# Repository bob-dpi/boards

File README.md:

# Boards
Some peripherals use common, off-the-shelf hardware such as
Pmod cards.  Some peripherals use custom hardware.  This
repository contains design files for peripherals that use 
custom hardware.

The [***contrib***](contrib/README.md)  directory has design
files for boards that have been contributed.  Each design is 
in its own directory, has its own LICENSE.txt, and should 
have a markdown file to describe the board.  

The [***dpi***](dpi/README.md) directory has the design files
for Demand Peripherals boards that can tolerate ringing
on long cable runs.  

<br>

| Contributed Designs from Several Sources | |
| :-- | :-- |
| <a href=contrib/pmgpiontw/pmgpio.md> Pmod compatible GPIO boards <br>  </a> | <a href=contrib/dpaamp/aamp.md> Stereo 2 Watt Amplifier with volume control <br>  </a> 
| <a href=contrib/dpd7hb/d7hb.md> Dual 7-amp H-bridge <br>  </a> | <a href=contrib/dpdrv4/drv4.md> Quad open-drain driver <br>  </a>
| <a href=contrib/dpirp8/irp8.md> Octal reflective sensor <br>  </a> | <a href=contrib/dprf315/rf315.md> Keyfob-type receiver <br>  </a>
| <a href=contrib/dprly410/rly410.md> Quad 10-amp relay card <br>  </a> | <a href=contrib/dproten/roten.md> Demand Peripherals rotary encoder with LED <br>  </a>
| <a href=contrib/dpsw4/sw4.md> Quad slide switch <br>  </a> | <a href=contrib/dptouch4/touch4.md> Quad low cost touch sensor <br>  </a>
| <a href=contrib/atxpd/atxpd.md> ATX power distribution card <br>  </a> | <a href=contrib/ddpd/ddpd.md> Molex disk-drive power distribution card <br>  </a>
| <a href=contrib/smr/smr.md> 5 volt switch mode regulator <br>  </a> | <a href=contrib/pd15/pd15.md> 15 amp power distribution card <br>  </a>
| <a href=contrib/pd25/pd25.md> 25 amp power distribution card <br>  </a> |  <a href=contrib/dpirio/irio.md> Consumer IR receiver and transmitter <br>  </a> |

<br>

| Daughter Cards from Demand Peripherals | |
| :-- | :-- |
|<a href=dpi/dpadc12/adc12.md> Octal 12-bit analog to digital converter<br>  </a> | <a href=dpi/dpdac8/dac8.md> Octal 8-bit digital to analog converter <br>  <br> </a> |
|<a href=dpi/dpei2c/ei2c.md> Ringing tolerant I2C interface<br>  </a> | <a href=dpi/dpespi/espi.md> Ringing tolerant SPI interface<br>  </a> |
|<a href=dpi/dpin32/in32.md> 32 channel binary input<br>  </a> | <a href=dpi/dpio8/io8.md> Octal input and output<br>  </a> |
|<a href=dpi/dplcd6/lcd6.md>  Six digit 7-segment display <br>  </a> | <a href=dpi/dpmega/mega.md> AVR card<br>  </a> |
|<a href=dpi/dpout32/out32.md> 32 channel binary output<br>  </a> | <a href=dpi/dpqpot/qpot.md> Quad 10K digital pot <br>  </a> |
|<a href=dpi/dprtc/rtc.md> Real-time clock with alarm <br>  </a> | <a href=dpi/dpslider4/slider4.md> Quad slide pot <br>  </a> |
|<a href=dpi/dptif/tif.md> Text interface card <br>  </a> | <a href=dpi/dpus8/us8.md> Octal HC-04 distance sensor interface <br>  </a> |

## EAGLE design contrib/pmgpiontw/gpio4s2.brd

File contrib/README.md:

# contrib
This directory has the hardware design files for peripherals that
need custom hardware.  There are also design files for some simple
accessories and for one FPGA card.  Each design is in its own directory,
has its own LICENSE.txt, and should have a markdown file that describes
the board.  

While many design use Eagle, the preferred format is KiCad.
<br>

## Peripheral Cards
[pmgpiontw](pmgpiontw/pmgpio.md): Pmod compatible GPIO boards from Demand Peripherals <br>
[dpaamp](dpaamp/aamp.md): Stereo 2 Watt Amplifier with volume control <br>
[dpd7hb](dpd7hb/d7hb.md): Dual 7-amp H-bridge <br>
[dpdrv4](dpdrv4/drv4.md): Quad open-drain driver <br>
[dpgpio4](dpgpio4/gpio4.md): Demand Peripherals quad GPIO cards <br>
[dpirio](dpirio/irio.md): Consumer IR receiver and transmitter <br>
[dpirp8](dpirp8/irp8.md): Octal reflective sensor <br>
[dprf315](dprf315/rf315.md): Keyfob-type receiver <br>
[dprly410](dprly410/rly410.md): Quad 10-amp relay card <br>
[dproten](dproten/roten.md): Demand Peripherals rotary encoder with LED <br>
[dpsw4](dpsw4/sw4.md): Quad slide switch <br>
[dptouch4](dptouch4/touch4.md): Quad low cost touch sensor <br>
<br>

## Accessories
[atxpd](atxpd/atxpd.md): ATX power distribution card <br>
[ddpd](ddpd/ddpd.md): Molex disk-drive power distribution card <br>
[smr](smr/smr.md): 5 volt switch mode regulator <br>
[pd15](pd15/pd15.md): 15 amp power distribution card <br>
[pd25](pd25/pd25.md): 25 amp power distribution card <br>
[protocards](protocards/protocards.md): Prototyping cards <br>

## FPGA Boards
[Baseboard4](Baseboard4/baseboard4.md): Demand Peripherals Spartan-3E FPGA card <br>

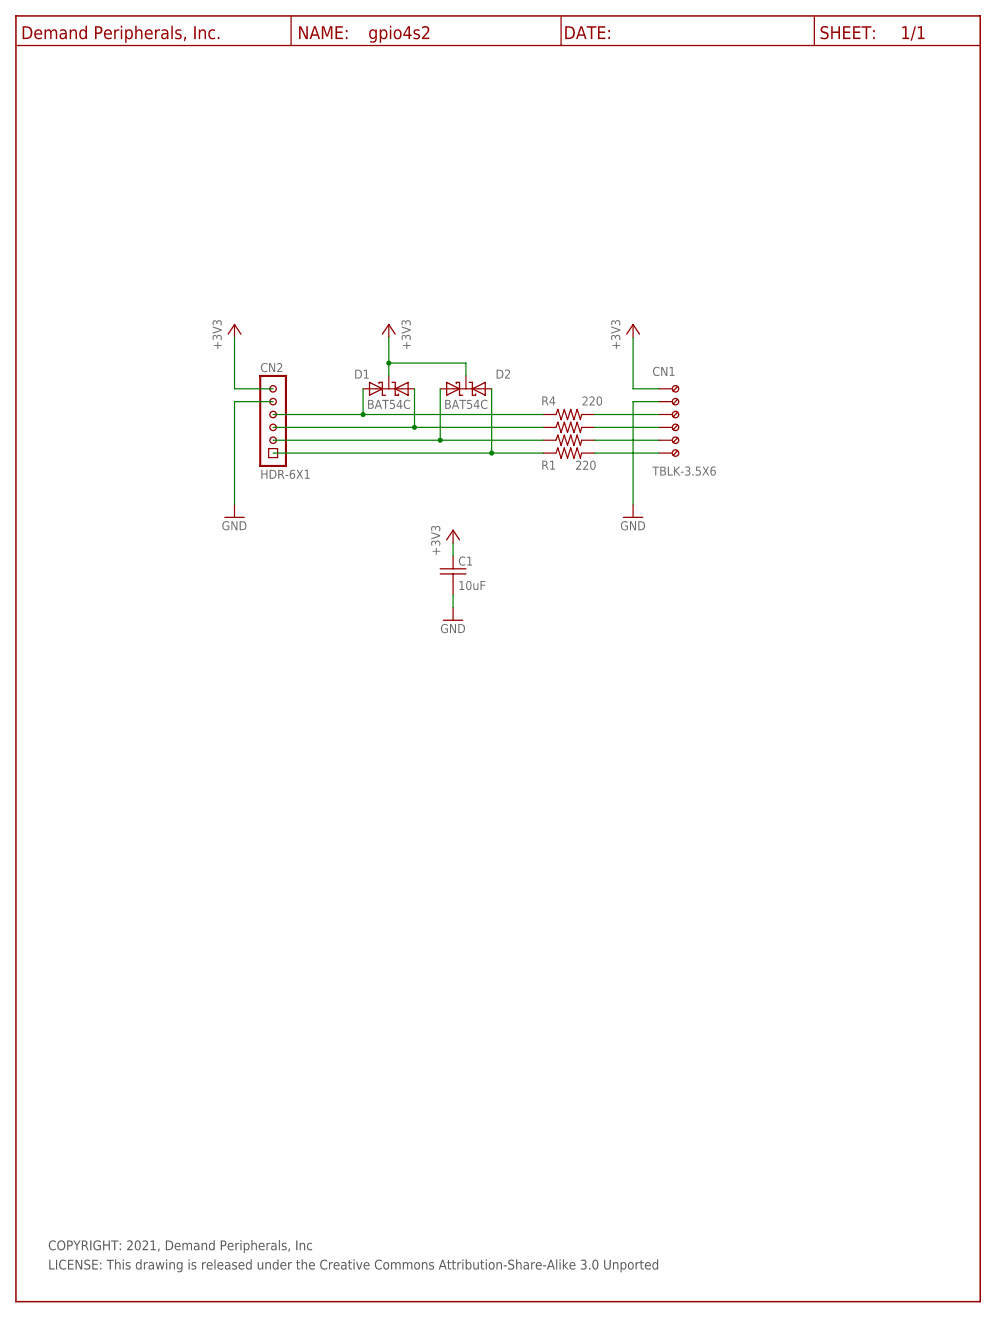
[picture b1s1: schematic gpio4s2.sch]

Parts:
C1: 10uF; C1206
CN1: TBLK-3.5X6
CN2: HDR-6X1
D1, D2: BAT54C; SOT23
R1, R2, R3, R4: 220; R0603
U$1: DP_FRAME_P; P_FRAME

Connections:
+3V3: C1.1, CN1.1 (KL), CN2.6, D1.3 (CC), D2.3 (CC)
GND: C1.2, CN1.2 (KL1), CN2.5
unnamed: CN1.3 (KL2), R4.2
unnamed: CN1.4 (KL3), R3.2
unnamed: CN1.5 (KL4), R2.2
unnamed: CN1.6 (KL5), R1.2
unnamed: CN2.4, D1.1 (A1), R4.1
unnamed: CN2.3, D1.2 (A), R3.1
unnamed: CN2.2, D2.1 (A1), R2.1
unnamed: CN2.1, D2.2 (A), R1.1

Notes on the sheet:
COPYRIGHT: 2021, Demand Peripherals, Inc
LICENSE: This drawing is released under the Creative Commons Attribution-Share-Alike 3.0 Unported

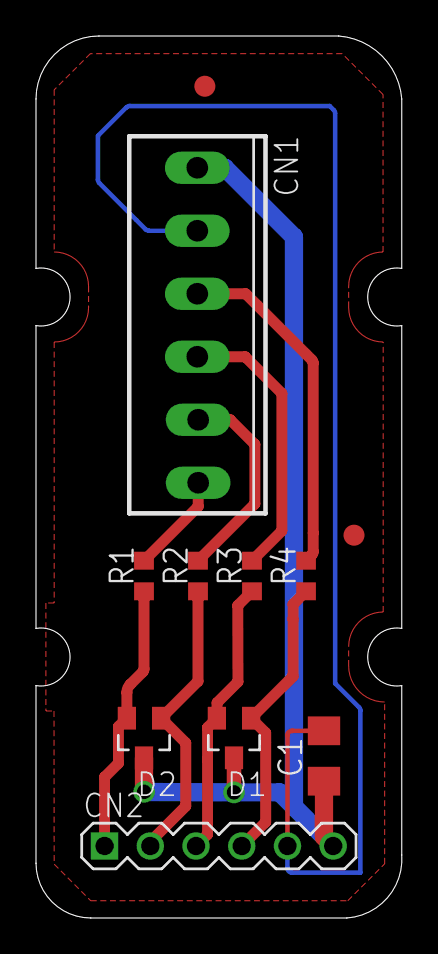
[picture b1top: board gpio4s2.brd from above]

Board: 2 copper layers, 20.3 x 49.0 mm, 13 parts (1 on the bottom side), 10 nets.

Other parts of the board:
U$2: DPI-2
U$3, U$8: FIDUCIAL

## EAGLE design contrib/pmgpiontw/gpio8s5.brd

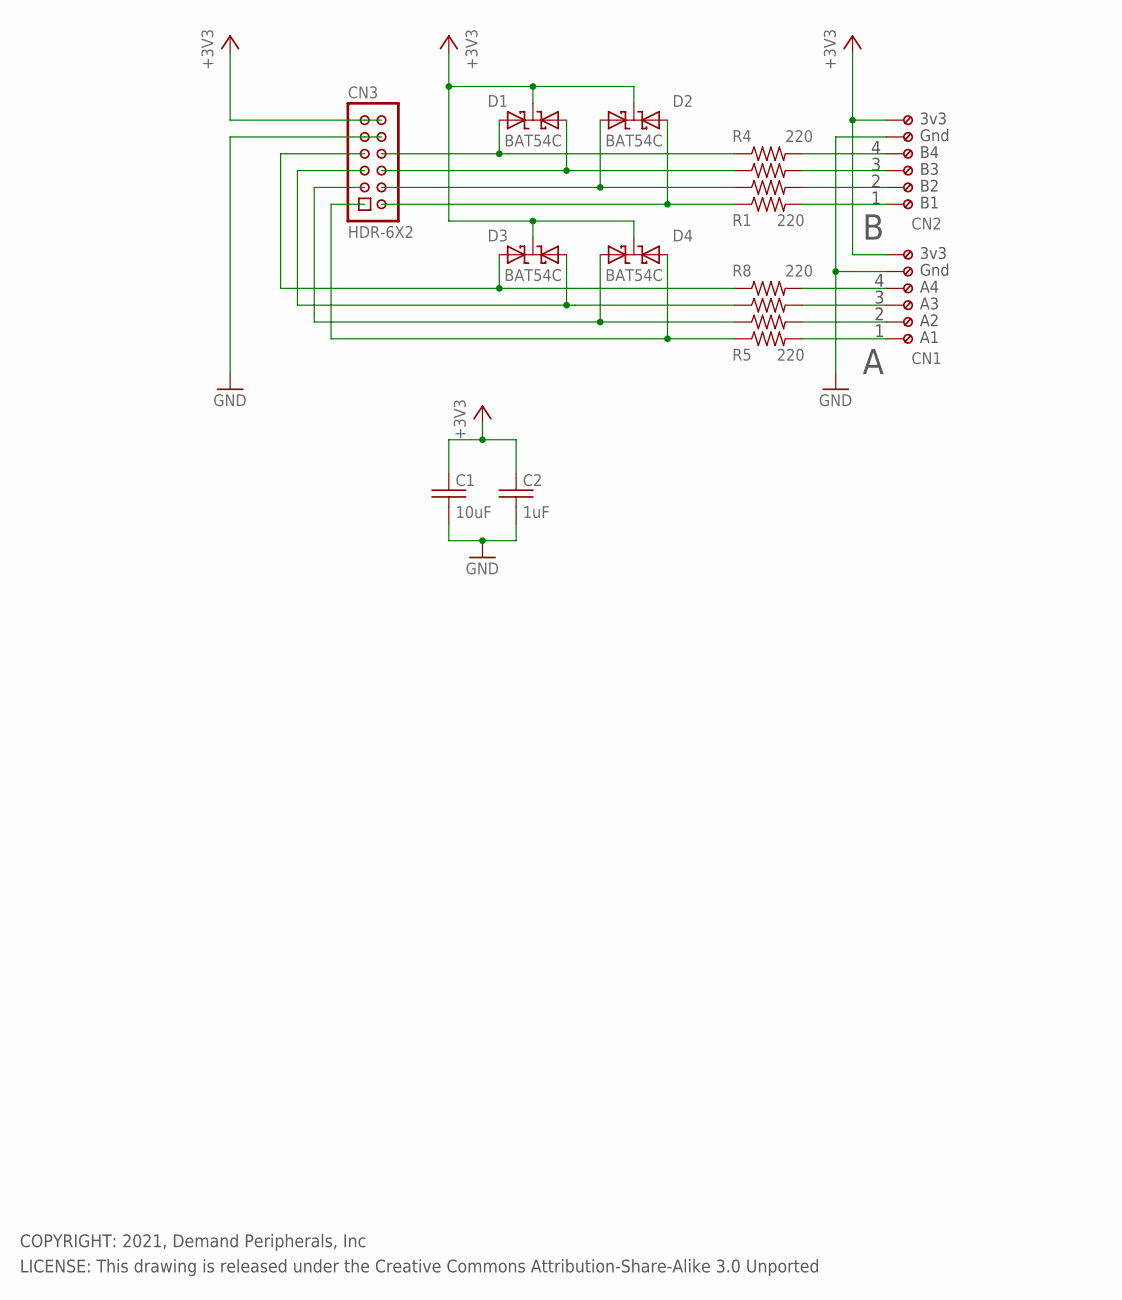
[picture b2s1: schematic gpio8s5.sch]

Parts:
C1: 10uF; C1206
C2: 1uF; C0603
CN1, CN2: TBLK-3.5X6
CN3: HDR-6X2
D1, D2, D3, D4: BAT54C; SOT23
R1, R2, R3, R4, R5, R6, R7, R8: 220; R0603

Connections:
+3V3: C1.1, C2.1, CN1.1 (KL), CN2.1 (KL), CN3.11, CN3.12, D1.3 (CC), D2.3 (CC), D3.3 (CC), D4.3 (CC)
GND: C1.2, C2.2, CN1.2 (KL1), CN2.2 (KL1), CN3.9, CN3.10
unnamed: CN2.3 (KL2), R4.2
unnamed: CN2.4 (KL3), R3.2
unnamed: CN2.5 (KL4), R2.2
unnamed: CN2.6 (KL5), R1.2
unnamed: CN3.7, D3.1 (A1), R8.1
unnamed: CN3.5, D3.2 (A), R7.1
unnamed: CN3.3, D4.1 (A1), R6.1
unnamed: CN3.1, D4.2 (A), R5.1
unnamed: CN1.3 (KL2), R8.2
unnamed: CN1.4 (KL3), R7.2
unnamed: CN3.8, D1.1 (A1), R4.1
unnamed: CN3.6, D1.2 (A), R3.1
unnamed: CN1.5 (KL4), R6.2
unnamed: CN3.4, D2.1 (A1), R2.1
unnamed: CN3.2, D2.2 (A), R1.1
unnamed: CN1.6 (KL5), R5.2

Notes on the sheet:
COPYRIGHT: 2021, Demand Peripherals, Inc
LICENSE: This drawing is released under the Creative Commons Attribution-Share-Alike 3.0 Unported
Gnd
3v3

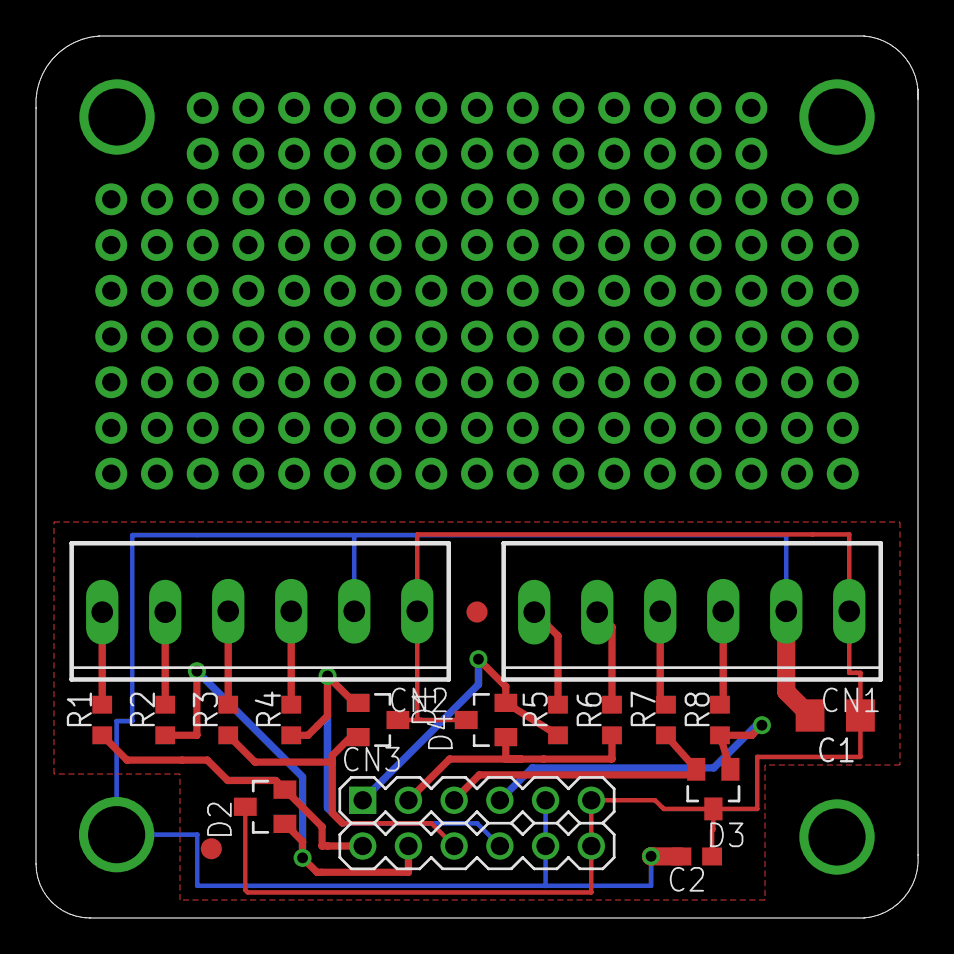
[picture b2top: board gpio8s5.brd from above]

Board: 2 copper layers, 49.0 x 49.0 mm, 20 parts (0 on the bottom side), 18 nets.

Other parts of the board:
U$2: DP_FRAME_P; P_FRAME
U$3, U$8: FIDUCIAL

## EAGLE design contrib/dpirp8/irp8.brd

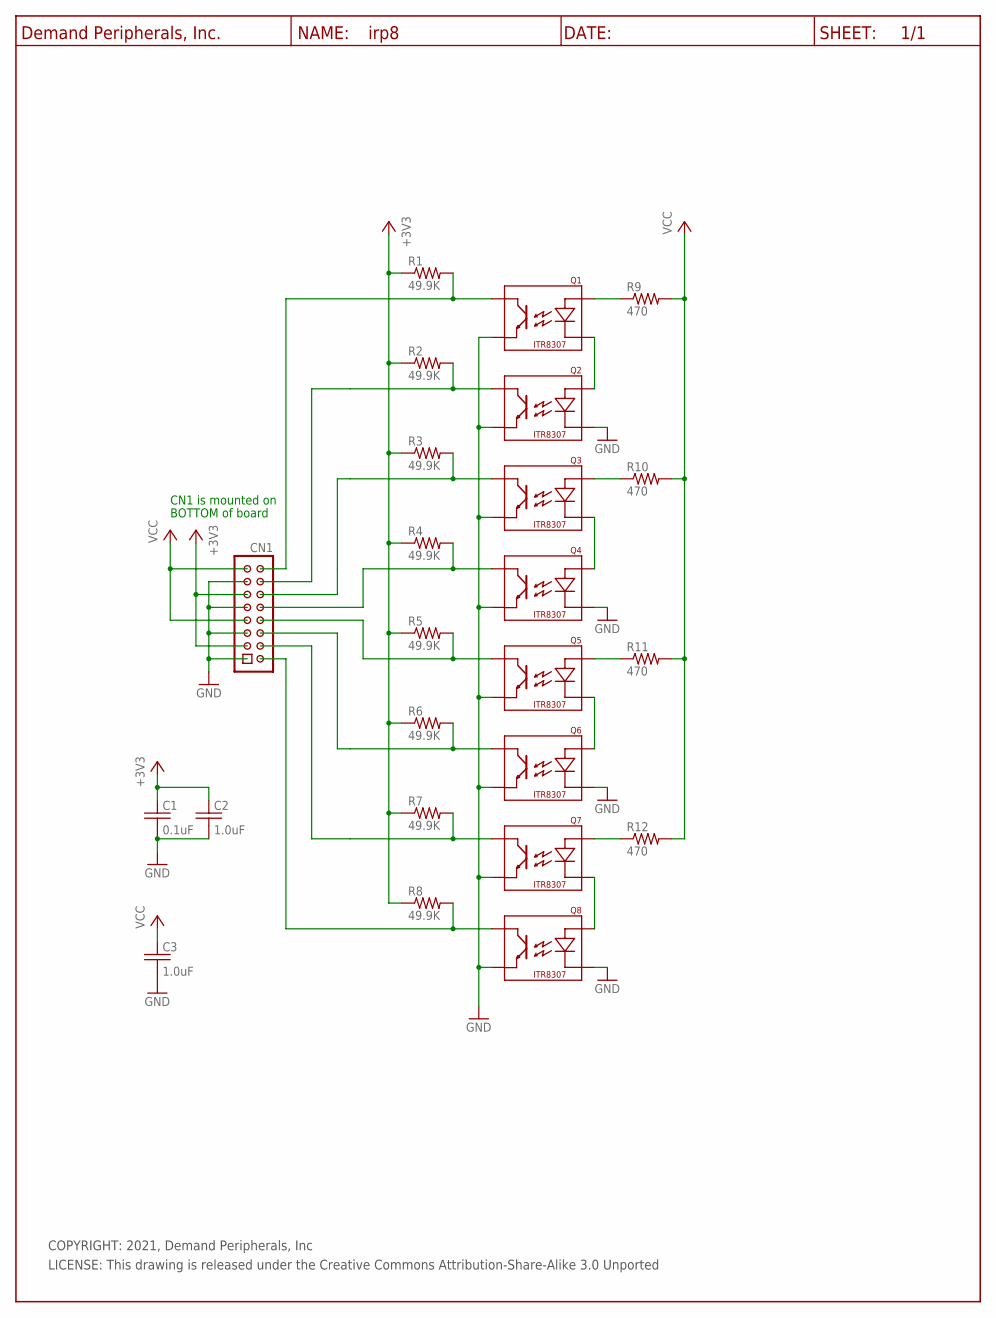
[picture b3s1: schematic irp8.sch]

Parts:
C1: 0.1uF; C0603
C2, C3: 1.0uF; C0603
CN1: HDR-8X2-SHR; HDR-8X2
Q1, Q2, Q3, Q4, Q5, Q6, Q7, Q8: ITR8307
R1, R2, R3, R4, R5, R6, R7, R8: 49.9K; R0603
R9, R10, R11, R12: 470; R0603
U$1: DP_FRAME_P; P_FRAME

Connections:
+3V3: C1.1, C2.1, CN1.3, CN1.11, R1.1, R2.1, R3.1, R4.1, R5.1, R6.1, R7.1, R8.1
GND: C1.2, C2.2, C3.2, CN1.1, CN1.5, CN1.9, CN1.13, Q1.P$1 (K), Q1.P$3 (CO), Q2.P$3 (CO), Q3.P$1 (K), Q3.P$3 (CO), Q4.P$3 (CO), Q5.P$1 (K), Q5.P$3 (CO), Q6.P$3 (CO), Q7.P$1 (K), Q7.P$3 (CO), Q8.P$3 (CO)
unnamed: CN1.16, Q8.P$4 (EM), R8.2
unnamed: Q2.P$2 (A), R12.1
unnamed: CN1.12, Q6.P$4 (EM), R6.2
unnamed: CN1.10, Q5.P$4 (EM), R5.2
unnamed: CN1.8, Q4.P$4 (EM), R4.2
unnamed: CN1.6, Q3.P$4 (EM), R3.2
unnamed: CN1.4, Q2.P$4 (EM), R2.2
unnamed: CN1.2, Q1.P$4 (EM), R1.2
unnamed: Q1.P$2 (A), Q2.P$1 (K)
unnamed: CN1.14, Q7.P$4 (EM), R7.2
unnamed: Q3.P$2 (A), Q4.P$1 (K)
unnamed: Q8.P$2 (A), R9.1
unnamed: Q7.P$2 (A), Q8.P$1 (K)
unnamed: Q6.P$2 (A), R10.1
unnamed: Q4.P$2 (A), R11.1
unnamed: Q5.P$2 (A), Q6.P$1 (K)
VCC: C3.1, CN1.7, CN1.15, R9.2, R10.2, R11.2, R12.2

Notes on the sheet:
COPYRIGHT: 2021, Demand Peripherals, Inc
LICENSE: This drawing is released under the Creative Commons Attribution-Share-Alike 3.0 Unported
CN1 is mounted on
BOTTOM of board

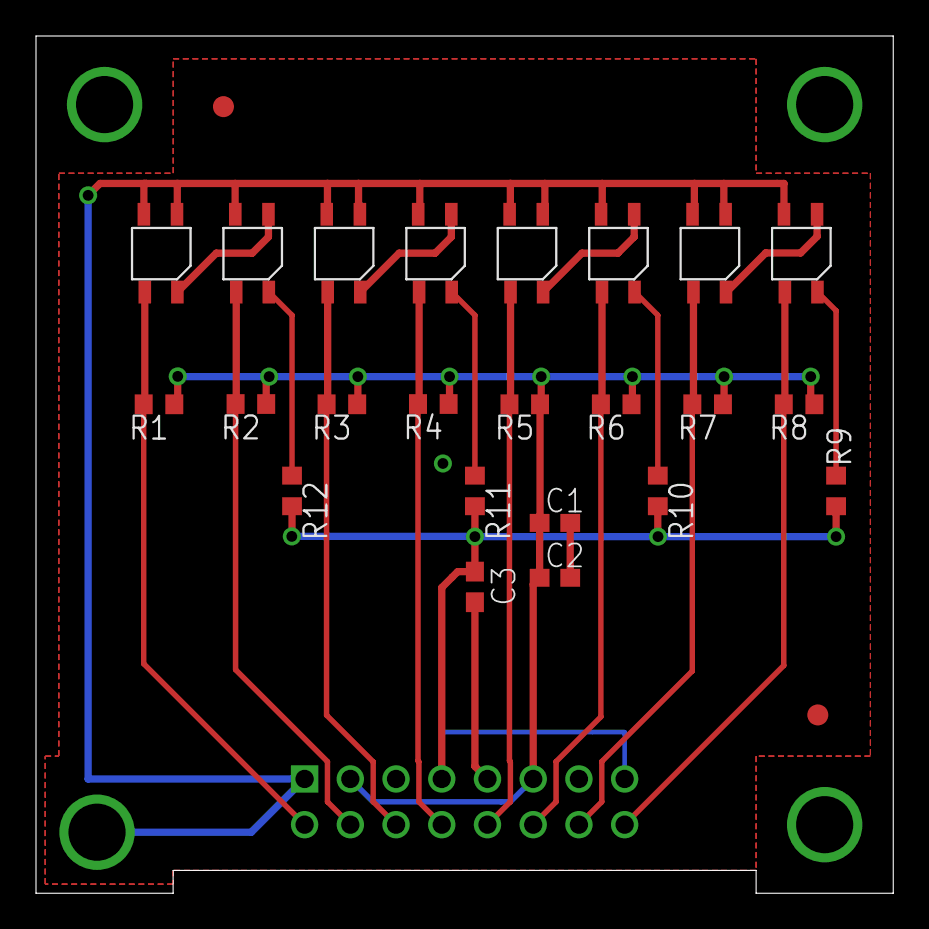
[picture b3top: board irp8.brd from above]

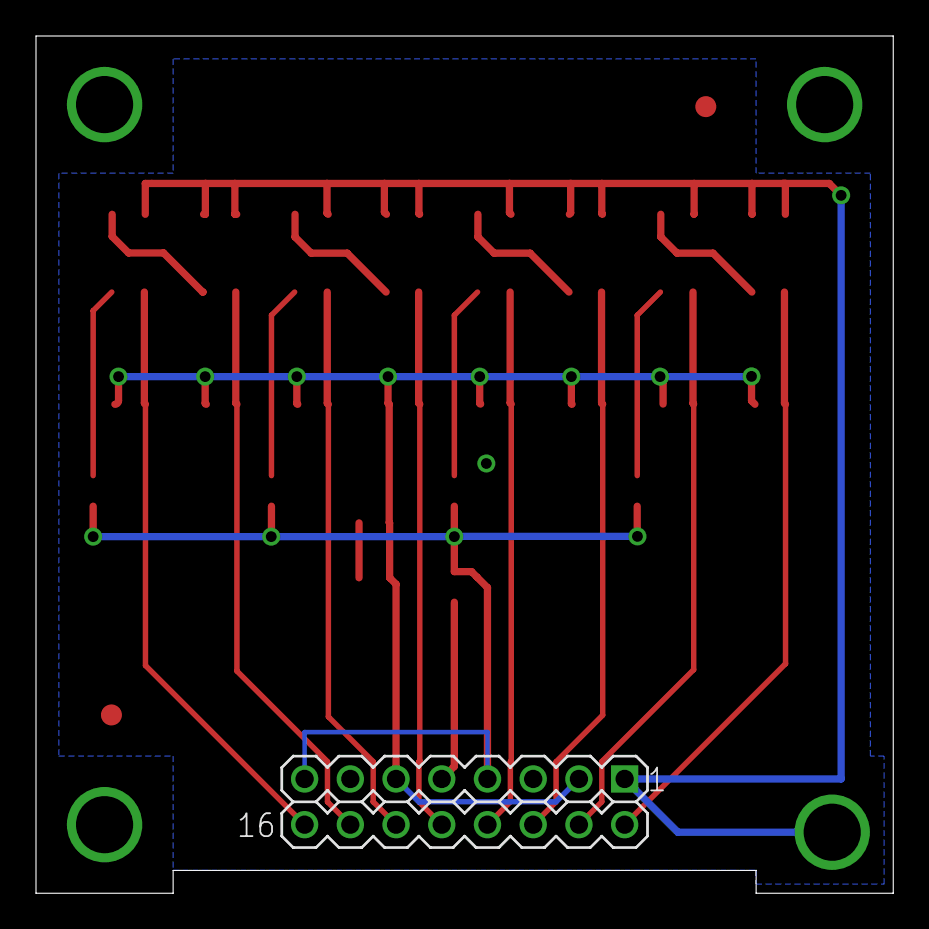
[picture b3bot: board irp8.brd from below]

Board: 2 copper layers, 47.6 x 47.6 mm, 28 parts (2 on the bottom side), 19 nets.

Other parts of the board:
U$2, U$3: FIDUCIAL
U$5: DPI-2

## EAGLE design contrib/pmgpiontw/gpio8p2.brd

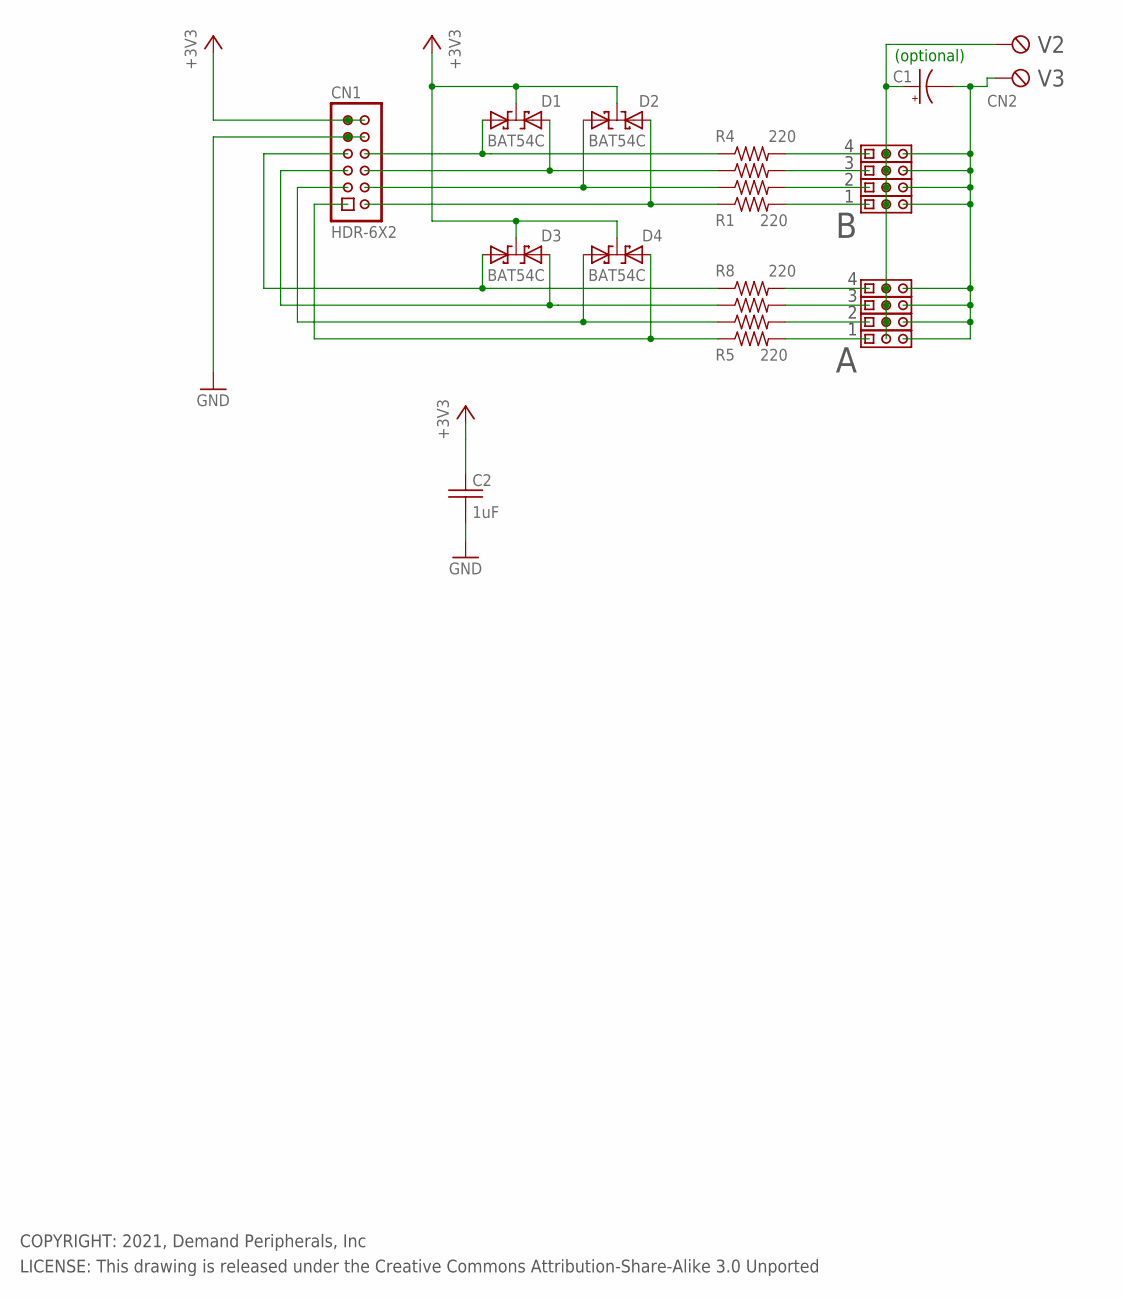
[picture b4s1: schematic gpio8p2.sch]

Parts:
C1: 100uF; E3.5-8
C2: 1uF; C0603
CN1: HDR-6X2
CN2: TBLK-5.08-X2
D1, D2, D3, D4: BAT54C; SOT23
R1, R2, R3, R4, R5, R6, R7, R8: 220; R0603
U$5, U$6, U$7, U$9, U$10, U$11, U$12, U$13: HDR-3X1

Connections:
+3V3: C2.1, CN1.11, CN1.12, D1.3 (CC), D2.3 (CC), D3.3 (CC), D4.3 (CC)
GND: C2.2, CN1.9, CN1.10
unnamed: R4.2, U$5.1
unnamed: R3.2, U$6.1
unnamed: R2.2, U$7.1
unnamed: R1.2, U$9.1
unnamed: C1.-, CN2.1 (KL), U$5.3, U$6.3, U$7.3, U$9.3, U$10.3, U$11.3, U$12.3, U$13.3
unnamed: CN1.7, D3.2 (A), R8.1
unnamed: CN1.5, D3.1 (A1), R7.1
unnamed: CN1.3, D4.2 (A), R6.1
unnamed: CN1.8, D1.2 (A), R4.1
unnamed: CN1.6, D1.1 (A1), R3.1
unnamed: CN1.1, D4.1 (A1), R5.1
unnamed: CN1.4, D2.1 (A1), R2.1
unnamed: CN1.2, D2.2 (A), R1.1
unnamed: R8.2, U$10.1
unnamed: R7.2, U$11.1
unnamed: C1.+, CN2.2 (KL1), U$5.2, U$6.2, U$7.2, U$9.2, U$10.2, U$11.2, U$12.2, U$13.2
unnamed: R6.2, U$12.1
unnamed: R5.2, U$13.1

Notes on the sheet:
(optional)
COPYRIGHT: 2021, Demand Peripherals, Inc
LICENSE: This drawing is released under the Creative Commons Attribution-Share-Alike 3.0 Unported

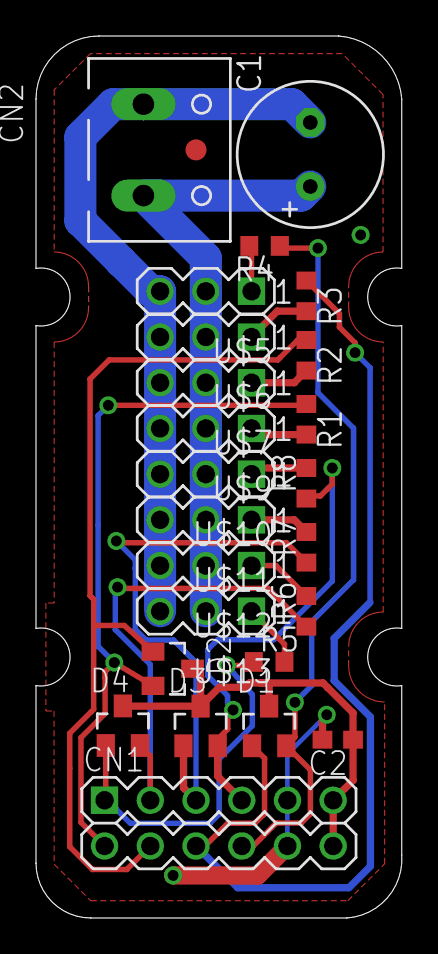
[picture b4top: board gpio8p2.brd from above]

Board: 2 copper layers, 20.3 x 49.0 mm, 26 parts (0 on the bottom side), 20 nets.

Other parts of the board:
U$2: DP_FRAME_P; P_FRAME
U$15: FIDUCIAL

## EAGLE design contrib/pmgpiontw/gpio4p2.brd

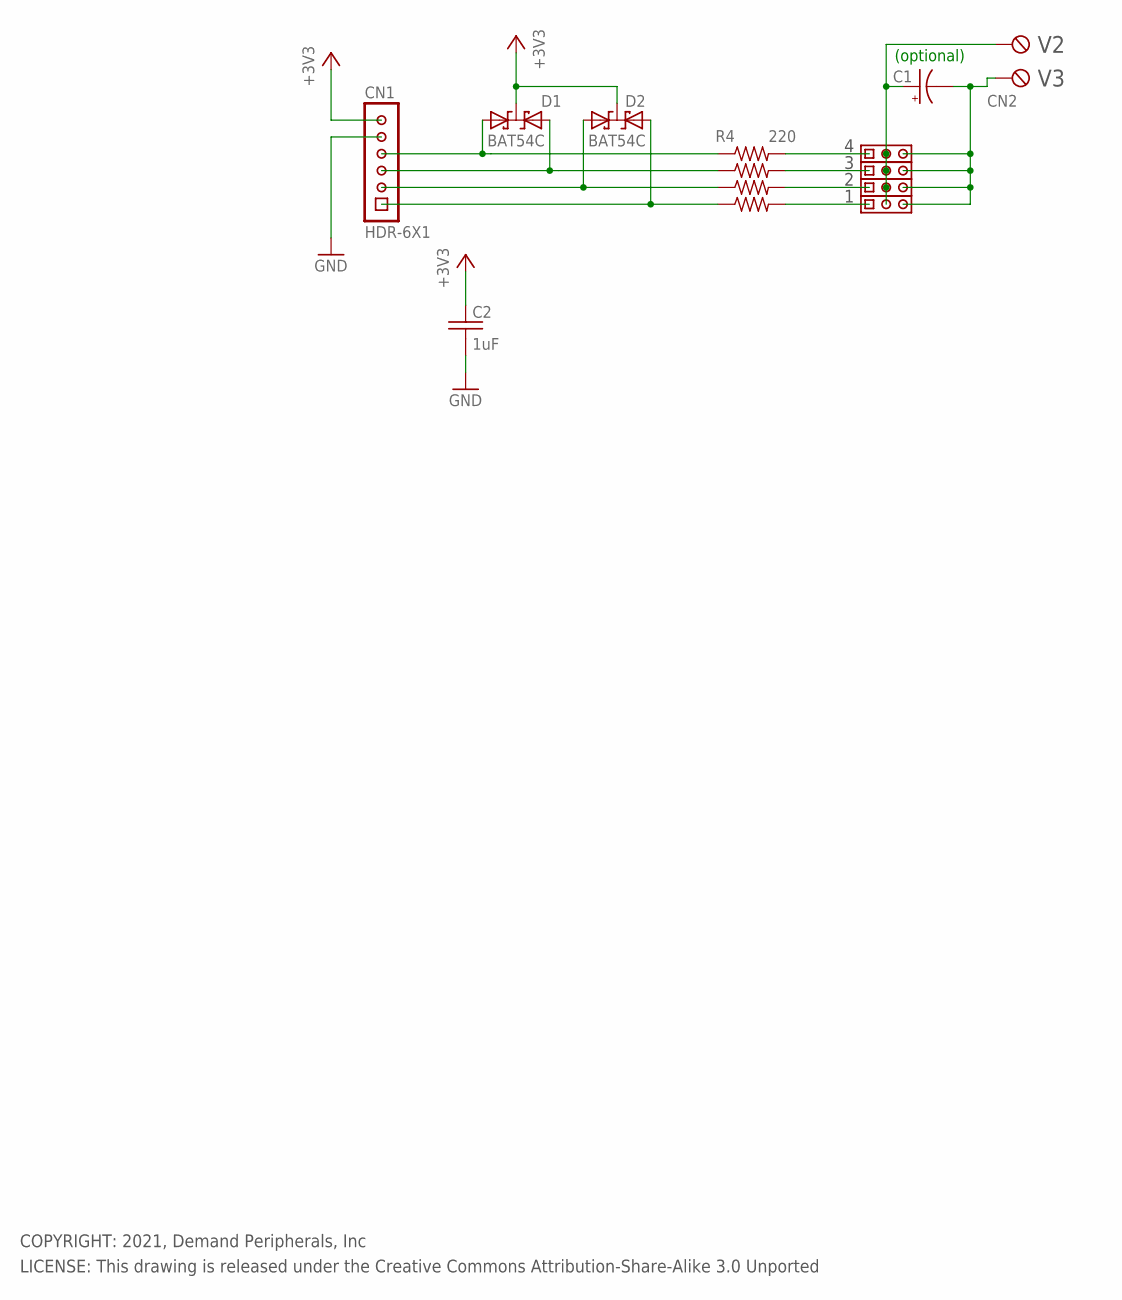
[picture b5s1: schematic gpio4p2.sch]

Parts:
C1: 100uF; E3.5-8
C2: 1uF; C0603
CN1: HDR-6X1
CN2: TBLK-5.08-X2
D1, D2: BAT54C; SOT23
R1, R2, R3, R4: 220; R0603
U$5, U$6, U$7, U$9: HDR-3X1

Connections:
+3V3: C2.1, CN1.6, D1.3 (CC), D2.3 (CC)
GND: C2.2, CN1.5
unnamed: R4.2, U$5.1
unnamed: R3.2, U$6.1
unnamed: R2.2, U$7.1
unnamed: R1.2, U$9.1
unnamed: C1.-, CN2.1 (KL), U$5.3, U$6.3, U$7.3, U$9.3
unnamed: CN1.4, D1.2 (A), R4.1
unnamed: CN1.3, D1.1 (A1), R3.1
unnamed: CN1.2, D2.2 (A), R2.1
unnamed: CN1.1, D2.1 (A1), R1.1
unnamed: C1.+, CN2.2 (KL1), U$5.2, U$6.2, U$7.2, U$9.2

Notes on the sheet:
(optional)
COPYRIGHT: 2021, Demand Peripherals, Inc
LICENSE: This drawing is released under the Creative Commons Attribution-Share-Alike 3.0 Unported

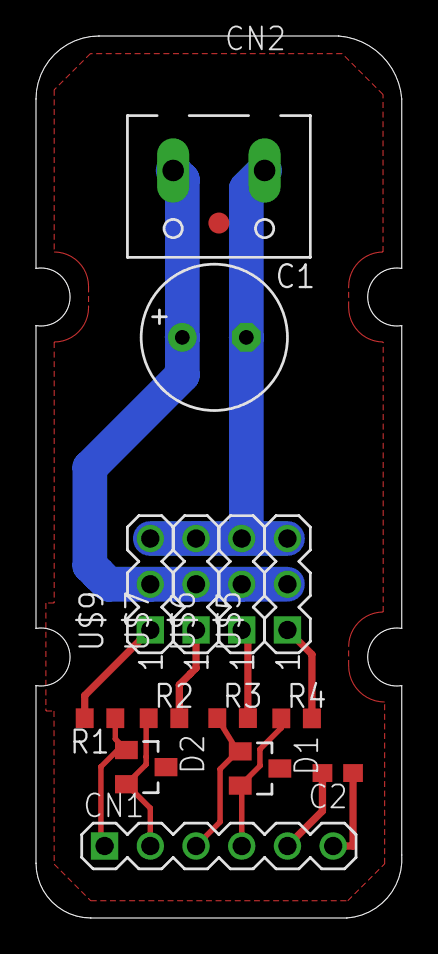
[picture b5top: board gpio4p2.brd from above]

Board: 2 copper layers, 20.3 x 49.0 mm, 17 parts (0 on the bottom side), 12 nets.

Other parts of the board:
U$1: DPI-2
U$2: DP_FRAME_P; P_FRAME
U$15: FIDUCIAL

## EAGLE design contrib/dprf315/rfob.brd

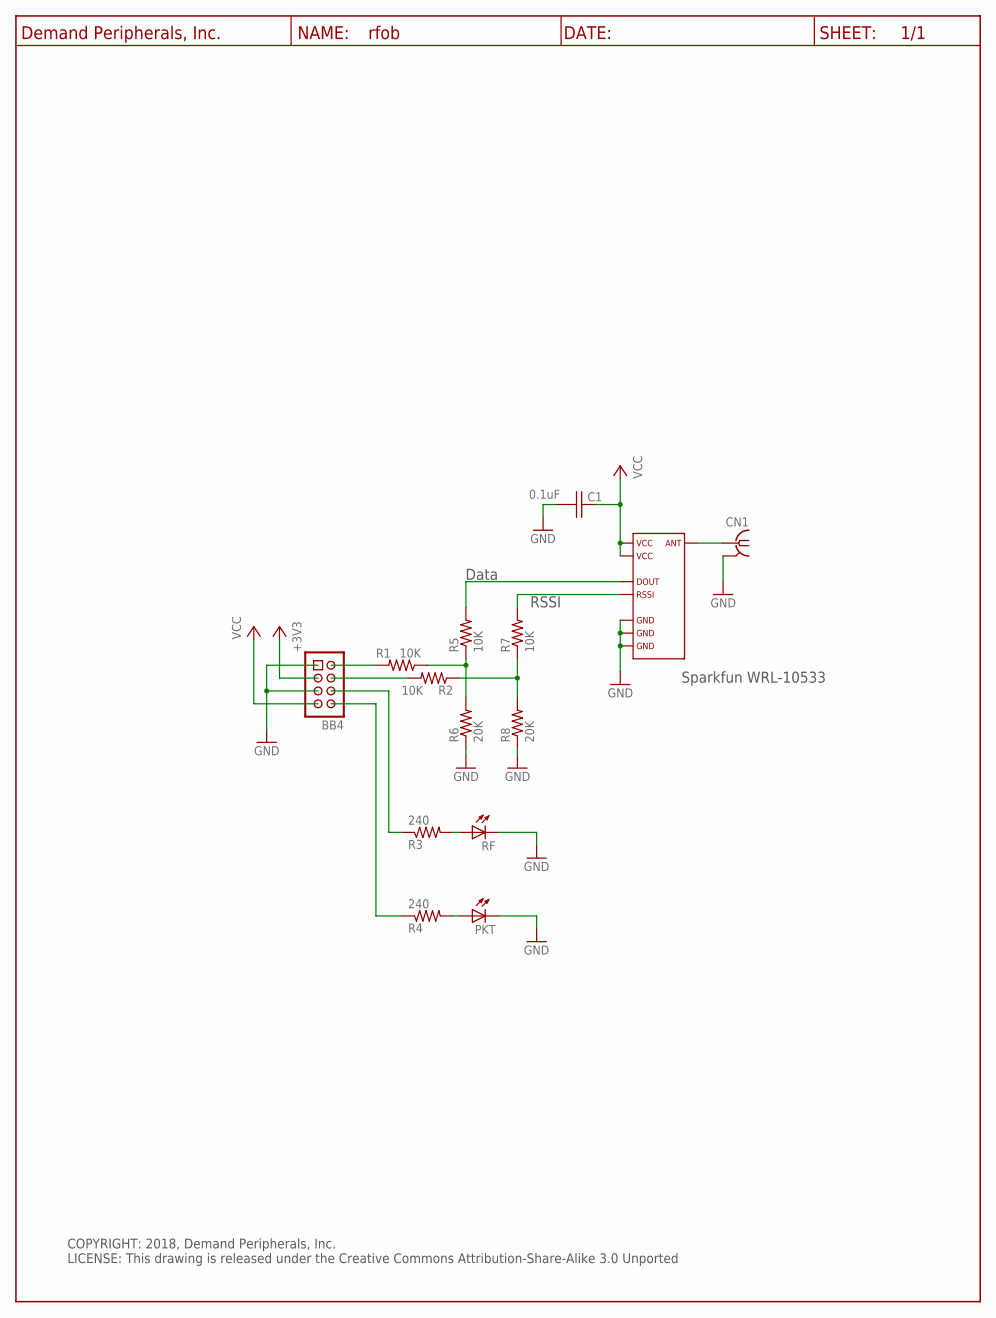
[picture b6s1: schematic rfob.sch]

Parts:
BB4: Keyed_Pin_Header_4x2(0.1"x0.1"); HDR-4X2
C1: 0.1uF; C0603
CN1: BU-SMA-V
PKT: LED-0805-RED; 0805
R1, R2, R5, R7: 10K; R0603
R3, R4: 240; R0603
R6, R8: 20K; R0603
RF: LED-0805-GRN; 0805
RF1: RFLINK
U$1: DP_FRAME_P; P_FRAME

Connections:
+3V3: BB4.3
GND: BB4.1, BB4.5, C1.2, CN1.2, CN1.3 (2), CN1.4 (2), CN1.5 (2), PKT.C, R6.1, R8.1, RF.C, RF1.1 (GND1), RF1.6 (GND3), RF1.7 (GND2)
unnamed: R3.2, RF.A
unnamed: BB4.6, R3.1
unnamed: R7.2, RF1.3 (RSSI)
unnamed: R2.1, R7.1, R8.2
unnamed: R1.1, R5.1, R6.2
unnamed: R5.2, RF1.2 (DOUT)
unnamed: BB4.8, R4.1
unnamed: PKT.A, R4.2
unnamed: BB4.2, R1.2
unnamed: BB4.4, R2.2
unnamed: CN1.1, RF1.8 (ANT)
VCC: BB4.7, C1.1, RF1.4 (VCC1), RF1.5 (VCC2)

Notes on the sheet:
RSSI
Data
Sparkfun WRL-10533
COPYRIGHT: 2018, Demand Peripherals, Inc. LICENSE: This drawing is released under the Creative Commons Attribution-Share-Alike 3.0 Unported

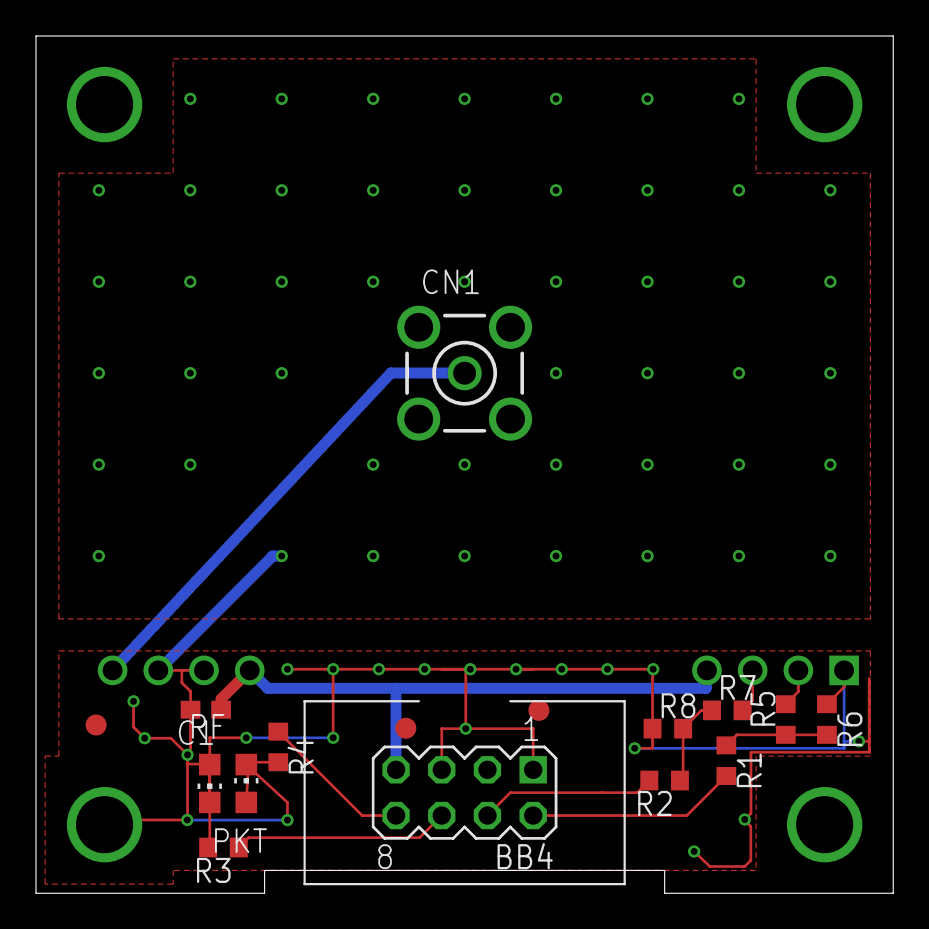
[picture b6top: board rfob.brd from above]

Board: 2 copper layers, 47.6 x 47.6 mm, 19 parts (1 on the bottom side), 13 nets.

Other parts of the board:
U$2, U$3, U$4: FIDUCIAL
U$5: DPI-2

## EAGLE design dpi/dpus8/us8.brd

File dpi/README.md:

## Daughter Cards from Demand Peripherals
[dpadc12](dpadc12/adc12.md): Octal 12-bit analog to digital converter <br>
[dpdac8](dpdac8/dac8.md): Octal 8-bit digital to analog converter <br>
[dpei2c](dpei2c/ei2c.md): Ringing tolerant I2C interface <br>
[dpespi](dpespi/espi.md): Ringing tolerant SPI interface <br>
[dpin32](dpin32/in32.md): 32 channel binary input <br>
[dpio8](dpio8/io8.md): Octal input and output <br>
[dplcd6](dplcd6/lcd6.md):  Six digit 7-segment display <br>
[dpmega](dpmega/mega.md): AVR card <br>
[dpout32](dpout32/out32.md): 32 channel binary output <br>
[dpqpot](dpqpot/qpot.md): Quad 10K digital pot <br>
[dprtc](dprtc/rtc.md): Real-time clock with alarm <br>
[dpslider4](dpslider4/slider4.md): Quad slide pot <br>
[dptif](dptif/tif.md): Text interface card <br>
[dpus8](dpus8/us8.md): Octal HC-04 distance sensor interface <br>

## Design Notes
All of the boards in this directory use a 7474 dual D-type flip-flop
to recover clean clock pulses even with ringing on all the lines 
from the FPGA.

The original Demand Peripherals FPGA board uses cables to connect to
daughter cards with the connectors or electronic for the peripheral.
Ribbon cables like this are an invitation for problems with ringing.

Traditional approaches use termination networks to **suppress** 
ringing, but suppression is not elimination and depending on the
cable length and frequency suppression can fail.

To overcome the problems of suppression the company decided to
**tolerate** ringing on the cables by quadrature encoding the clock
and using a D flip-flop to recover the clock.  This timing diagram
shows how the Q output of the D flip-flop does not have ringing and
could be used as a clean clock source for shift registers, SPI, or
I2C.  This circuit can also fail due to ringing but for frequencies
in the megahertz range the cable lenght to cause problems is very
long.

Using a quadrature encoded clock solves the ringing problem but 
requires an extra pin from the FPGA.  Since both Pmod and Demand
peripherals card have four FPGA pins this approach will not work
for SPI or shift registers with both output and input.  Demand
Peripherals solved this problem by using the second D flip-flop
in the 7474 to latch the chip select line.  The following schematic
shows the final circuit.

This circuit is protected by US Patent Number 10,324,889 which is
assigned to Demand Peripherals.  The circuit is free to use for
non-commercial projects and a 15 year license costs less than one
hundred dollars for commercial projects.  If you want long cable
runs you should use this circuit.

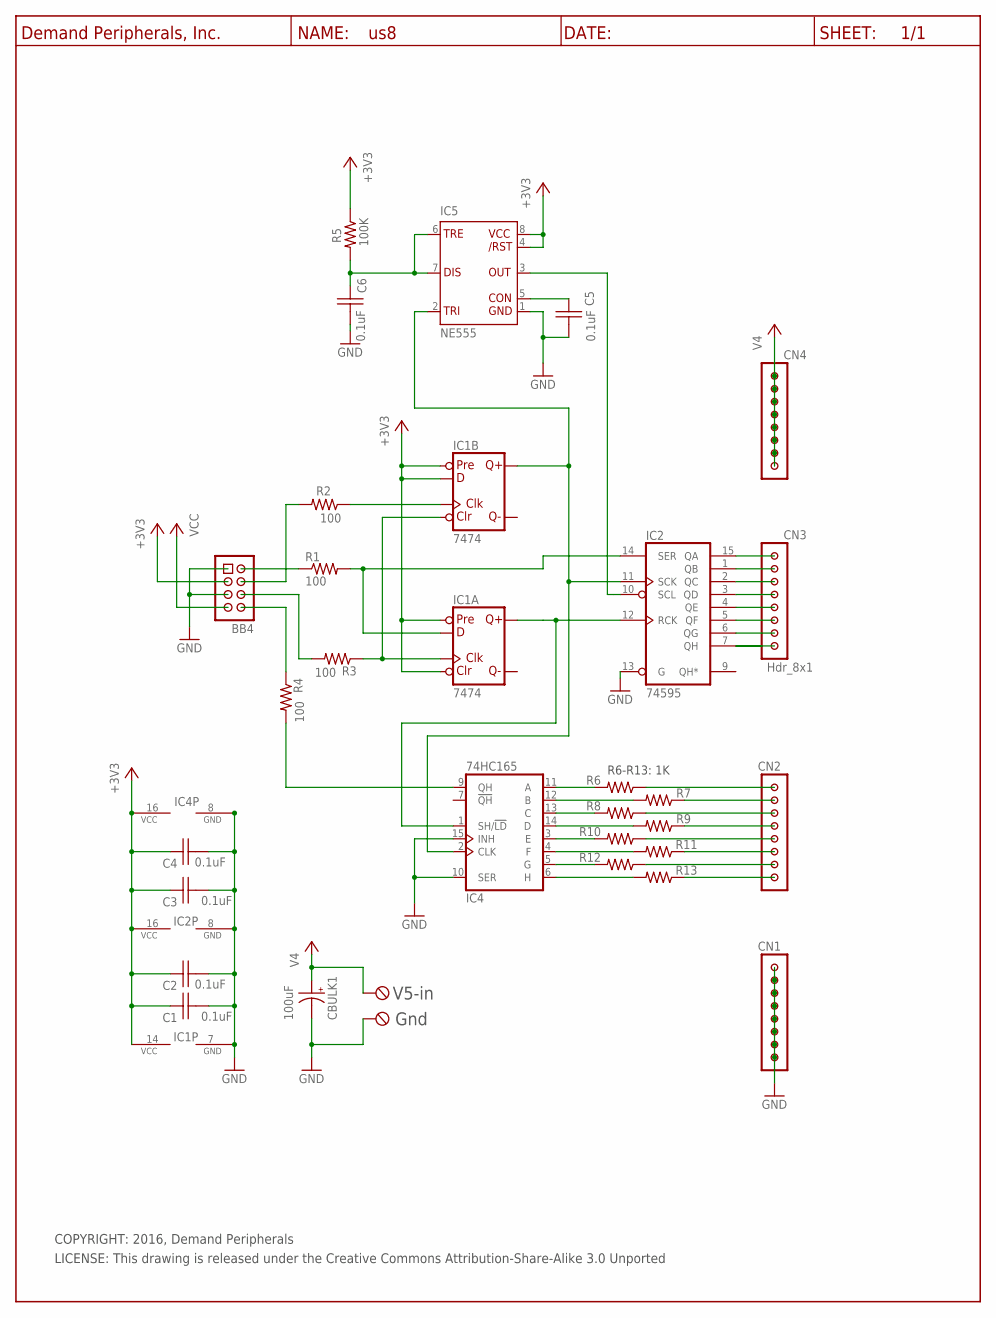
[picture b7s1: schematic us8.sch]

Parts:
BB4: Hdr_4x2; HDR-4X2
C1, C2, C3, C4, C5, C6: 0.1uF; C0603
CBULK1: 100uF; E3.5-8
CN1, CN2, CN3, CN4: Hdr_8x1; HDR-8X1-NOP1
CN5: TBLK-5.08-X2
IC1: 7474; SO14
IC2: 74595; SO16
IC4: 74HC165; SO16
IC5: NE555; SOIC8
R1, R2, R3, R4: 100; R0603
R5: 100K; R0603
R6, R7, R8, R9, R10, R11, R12, R13: 1K; R0603
U$4: DP_FRAME_P; P_FRAME

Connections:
+3V3: BB4.3, C1.1, C2.1, C3.1, C4.1, IC1.1 (CLR), IC1.4 (PRE), IC1.10 (PRE), IC1.12 (D), IC1.14 (VCC), IC2.16 (VCC), IC4.16 (VCC), IC5.4 (/RES), IC5.8 (VCC+), R5.1
GND: BB4.1, BB4.5, C1.2, C2.2, C3.2, C4.2, C5.2, C6.2, CBULK1.-, CN1.1, CN1.2, CN1.3, CN1.4, CN1.5, CN1.6, CN1.7, CN1.8, CN5.1 (KL), IC1.7 (GND), IC2.8 (GND), IC2.13 (G), IC4.8 (GND), IC4.10 (SER), IC4.15 (INH), IC5.1 (GND)
unnamed: BB4.2, R1.1
unnamed: BB4.8, R4.1
unnamed: CN2.1, R13.1
unnamed: CN2.2, R12.1
unnamed: CN2.3, R11.1
unnamed: IC1.2 (D), IC2.14 (SER), R1.2
unnamed: CN2.4, R10.1
unnamed: CN2.5, R9.1
unnamed: CN2.6, R8.1
unnamed: CN2.7, R7.1
unnamed: CN2.8, R6.1
unnamed: IC4.11 (A), R6.2
unnamed: IC4.13 (C), R8.2
unnamed: CN3.1, IC2.7 (QH)
unnamed: IC1.3 (CLK), IC1.13 (CLR), R3.1
unnamed: IC1.9 (Q), IC2.11 (SCK), IC4.2 (CLK), IC5.2 (TRI)
unnamed: BB4.4, R2.2
unnamed: IC1.11 (CLK), R2.1
unnamed: BB4.6, R3.2
unnamed: IC4.9 (QH), R4.2
unnamed: CN3.2, IC2.6 (QG)
unnamed: CN3.3, IC2.5 (QF)
unnamed: CN3.4, IC2.4 (QE)
unnamed: CN3.5, IC2.3 (QD)
unnamed: CN3.6, IC2.2 (QC)
unnamed: CN3.7, IC2.1 (QB)
unnamed: CN3.8, IC2.15 (QA)
unnamed: IC4.3 (E), R10.2
unnamed: IC4.5 (G), R12.2
unnamed: IC4.12 (B), R7.2
unnamed: IC4.14 (D), R9.2
unnamed: IC4.4 (F), R11.2
unnamed: IC4.6 (H), R13.2
unnamed: IC1.5 (Q), IC2.12 (RCK), IC4.1 (SH/!LD)
unnamed: IC2.10 (SCL), IC5.3 (OUT)
unnamed: C6.1, IC5.6 (TRE), IC5.7 (DIS), R5.2
unnamed: C5.1, IC5.5 (CON)
V4: CBULK1.+, CN4.1, CN4.2, CN4.3, CN4.4, CN4.5, CN4.6, CN4.7, CN4.8, CN5.2 (KL1)
VCC: BB4.7

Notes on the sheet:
Gnd
V5-in
R6-R13: 1K
COPYRIGHT: 2016, Demand Peripherals
LICENSE: This drawing is released under the Creative Commons Attribution-Share-Alike 3.0 Unported

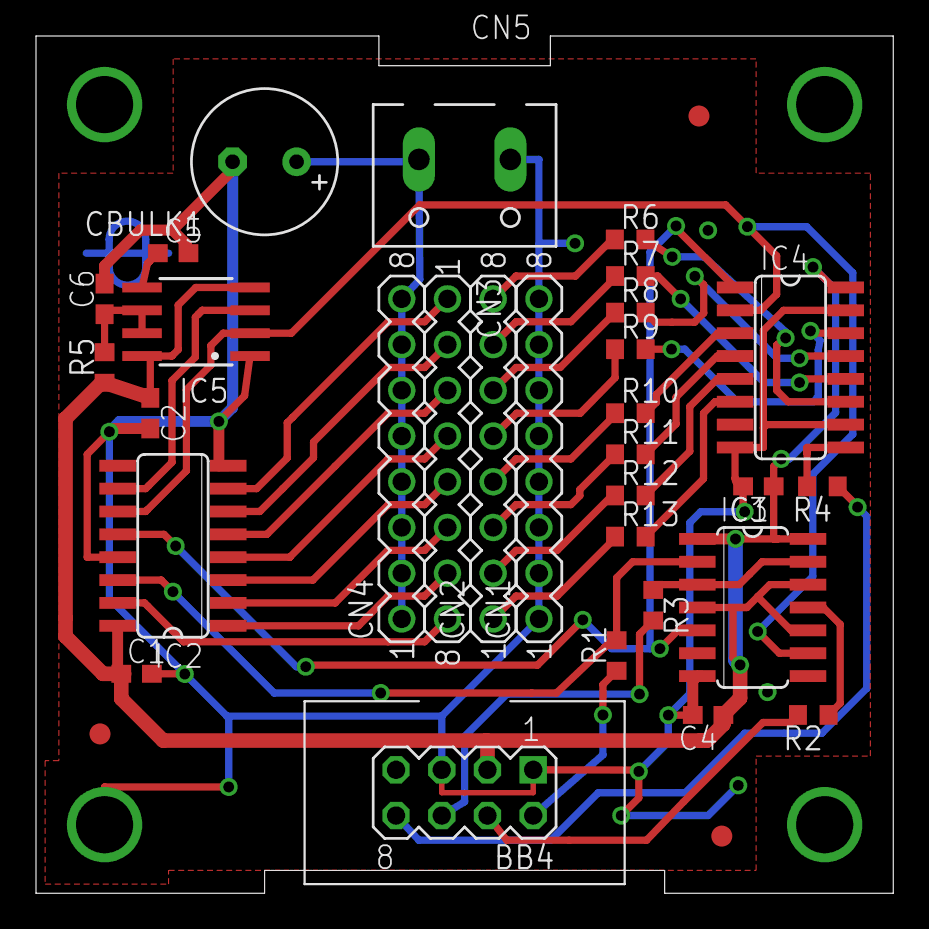
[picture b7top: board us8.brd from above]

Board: 2 copper layers, 47.6 x 47.6 mm, 35 parts (1 on the bottom side), 40 nets.

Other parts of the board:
U$1, U$2, U$3: FIDUCIAL
U$6: DPI-1

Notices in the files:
contrib/dpirp8/irp8.brd:
(C) 2021, Demand Peripherals, Inc.
contrib/dprf315/rfob.brd:
(C) 2017, Demand Peripherals, Inc.
